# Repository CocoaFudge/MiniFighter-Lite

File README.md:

# MiniFighter-Lite

MAKE SURE TO USE THE FINAL FILES FOR ADOBE ILLUSTRATOR. THANKS!

Free to modify, use, recreate.

Please credit if modifying the PCB. :)

Parts needed :

5X M6 X 14MM Screw, not countersunk,

5X M6 Screw Bolts,

12 x MX Hotswap Sockets,

12 x MX Switches,

12 x Punk Workshop / Sinoarcade MX Keycaps, either 24 or 30mm works,

01 x BOB-15100 / Treedix USB-C Breakout board,

01 x MiniFighter Lite PCB,

01 x Minifighter Lite Switchplate,

01 x MiniFighter Lite Acrylic Switchplate (3mm),

01 x Case enclosure,

will add instructions and case design files. ignore the crack

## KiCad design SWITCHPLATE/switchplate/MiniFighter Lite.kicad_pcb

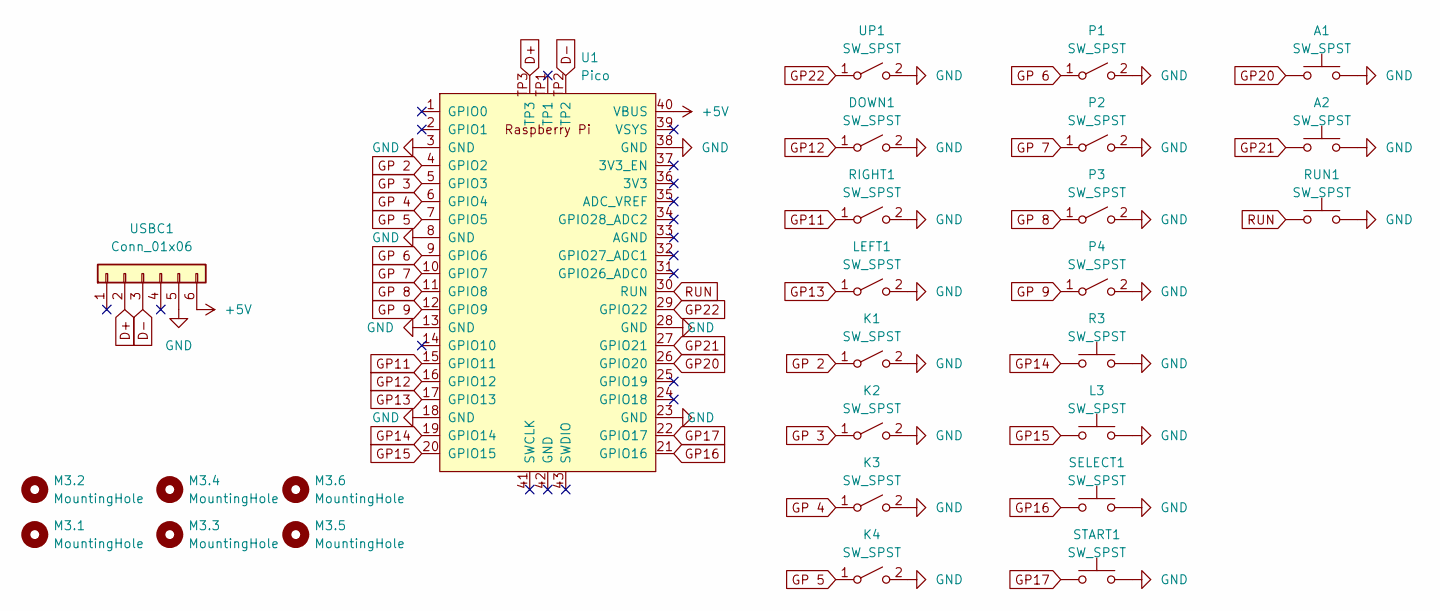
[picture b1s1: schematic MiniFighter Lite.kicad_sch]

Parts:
A1, A2: SW_SPST; SW_PUSH_6mm
DOWN1: SW_SPST; SW_Hotswap_Kailh_MX
K1, K2, K3, K4: SW_SPST; SW_Hotswap_Kailh_MX
L3: SW_SPST; SW_PUSH_6mm
LEFT1: SW_SPST; SW_Hotswap_Kailh_MX
M3.1, M3.2, M3.3, M3.4, M3.5, M3.6: MountingHole; MountingHole_3.2mm_M3
P1, P2, P3, P4: SW_SPST; SW_Hotswap_Kailh_MX
R3: SW_SPST; SW_PUSH_6mm
RIGHT1: SW_SPST; SW_Hotswap_Kailh_MX
RUN1: SW_SPST; SW_PUSH_6mm
SELECT1: SW_SPST; SW_PUSH_6mm
START1: SW_SPST; SW_PUSH_6mm
U1: Pico; Pi_Pico_W_BIG_TP_HOLE
UP1: SW_SPST; SW_Hotswap_Kailh_MX
USBC1: Conn_01x06; treedix usb-c

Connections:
+5V: U1.40 (VBUS), USBC1.6
D+: U1.TP3, USBC1.2
D-: U1.TP2, USBC1.3
GND: A1.2, A2.2, DOWN1.2 (B), K1.2 (B), K2.2 (B), K3.2 (B), K4.2 (B), L3.2, LEFT1.2 (B), P1.2 (B), P2.2 (B), P3.2 (B), P4.2 (B), R3.2, RIGHT1.2 (B), RUN1.2, SELECT1.2, START1.2, U1.3 (GND), U1.8 (GND), U1.13 (GND), U1.18 (GND), U1.23 (GND), U1.28 (GND), U1.38 (GND), UP1.2 (B), USBC1.5
GP11: RIGHT1.1 (A), U1.15 (GPIO11)
GP12: DOWN1.1 (A), U1.16 (GPIO12)
GP13: LEFT1.1 (A), U1.17 (GPIO13)
GP14: R3.1, U1.19 (GPIO14)
GP15: L3.1, U1.20 (GPIO15)
GP16: SELECT1.1, U1.21 (GPIO16)
GP17: START1.1, U1.22 (GPIO17)
GP20: A1.1, U1.26 (GPIO20)
GP21: A2.1, U1.27 (GPIO21)
GP22: U1.29 (GPIO22), UP1.1 (A)
GP 2: K1.1 (A), U1.4 (GPIO2)
GP 3: K2.1 (A), U1.5 (GPIO3)
GP 4: K3.1 (A), U1.6 (GPIO4)
GP 5: K4.1 (A), U1.7 (GPIO5)
GP 6: P1.1 (A), U1.9 (GPIO6)
GP 7: P2.1 (A), U1.10 (GPIO7)
GP 8: P3.1 (A), U1.11 (GPIO8)
GP 9: P4.1 (A), U1.12 (GPIO9)
RUN: RUN1.1, U1.30 (RUN)

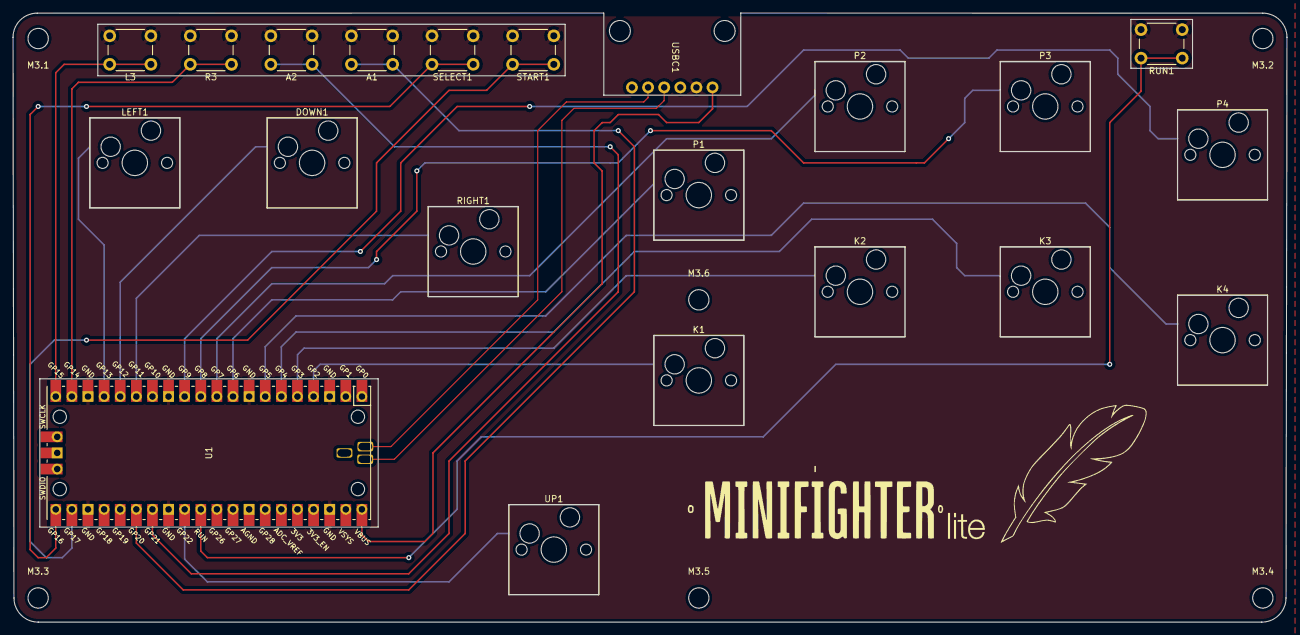
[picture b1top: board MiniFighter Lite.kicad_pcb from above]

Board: 2 copper layers, 200.8 x 96.0 mm, 30 parts (0 on the bottom side), 23 nets.

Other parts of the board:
0: LOGO
O: LOGO
_: LOGO

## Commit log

2022-07-03 Update LICENSE
2022-07-12 added kicad files
2022-08-05 Use FINAL.AI For laser cutting service
